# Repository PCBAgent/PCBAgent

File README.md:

# PCBAgent-GX10

PCBAgent takes one circuit request and, with no further input, designs a private board on the ASUS Ascent GX10: simulated, sourced, and routed offline.

A schematic is the product. Part values, pinouts, and the board outline should not have to leave the machine before software can help. PCBAgent runs that work on the GX10, an ultra-small AI computer with the NVIDIA GB10 Grace Blackwell Superchip and 128 GB of unified memory. Nemotron, ngspice, a local JLCPCB catalog, KiCad, and Freerouting all run on the box. Unplugging the network does not stop a design.

## Why local

Cloud schematic tools upload the design before they answer. Here the model and the checkers share the machine where the design is created. There is no cloud round trip, no vendor API for the netlist, and no infrastructure to keep up for a single board. The same flow still runs with the network disconnected.

## What it does

One request becomes a checked board. The model writes the circuit. SPICE, the parts catalog, the placer, and KiCad decide whether that circuit is true. After the first prompt, the run continues on its own until you cancel it, and you can watch placement and routing in KiCad while it does.

1. **Specify and simulate.** `/design` writes a circuit spec and a SKiDL file. SKiDL emits a SPICE netlist, and ngspice runs it. The model does not hand-write a simulator deck.
2. **Verify.** Each acceptance number in the spec, such as output voltage and current, is compared with the ngspice measurement inside the stated tolerance. A value counts only when that simulation produced it. A miss stays inside `/design`: the model changes the circuit and the same checks run again. It does not edit the spec to hide a failure.
3. **Select parts and write the netlist.** Passives and the regulator are matched to a local JLCPCB catalog. Stock, price, and footprint names are copied from that cache and from the installed KiCad libraries. The same connections become a KiCad netlist with those symbols and footprints.
4. **Place and route.** `/layout` asks the model for placement constraints, such as a capacitor next to its IC. It does not emit coordinates or traces. A placer chooses positions, Freerouting draws the copper, and KiCad's design-rule check scores the board. `layout.py --demo` records that sequence and plays it in the PCB editor with no further prompts.

## Demo

Two finished boards are in `designs/`:

- `5v-to-3v3-divider`, a 5 V to 3.3 V divider into a 33 ohm load
- `5v-to-3v3-ldo-10uf-22uf-33ohm-25x20mm-jlcpcb`, the same request on an AMS1117-3.3 with 10 µF in and 22 µF out

Replay the routed board in the KiCad PCB Editor from the GX10 desktop. Enable **Preferences → Plugins → Enable KiCad API** first.

```bash
source .venv/bin/activate
.venv/bin/python skills/layout/demo.py designs/5v-to-3v3-ldo-10uf-22uf-33ohm-25x20mm-jlcpcb --replay
```

Parts move into place, then the copper appears. `layout/board.png` in the same design is the still image of the routed board. To record a new animation while laying out again, run `skills/layout/layout.py designs/<slug> --demo`.

A new design starts in Pi with a single command, for example:

```text
/design 5 V supply to 3.3 V LDO using one linear regulator IC, a 10 µF input capacitor, and a 22 µF output capacitor, output voltage 3.3 V within 0.05 V, output current 0.1 A within 0.01 A into a 33 ohm load, maximum board size 25 mm by 20 mm, JLCPCB
```

## Chat window

The same agent, in its own window instead of the terminal. Skills, commands, and checks are unchanged. On the GX10 desktop:

```bash
python3 chat/window.py
```

`/design` and the rest of the flow work as they do in `pi`. Close the window to stop that session.

## Run it on the GX10

KiCad 9 or newer is installed separately. From this checkout:

```bash
./setup.sh
source .venv/bin/activate
ollama list
```

`setup.sh` installs Pi and `uv` when they are missing, installs SKiDL into `.venv`, and downloads Freerouting 2.5.0. Use an exact model id from `ollama list`. Start the Ollama bridge in one terminal:

```bash
export PCB_OLLAMA_MODEL=<id from ollama list>
.venv/bin/python tools/ollama_bridge.py
```

In another terminal, from this checkout:

```bash
export PCB_OLLAMA_MODEL=<id from ollama list>
pi --provider pcb-ollama --model "$PCB_OLLAMA_MODEL" --thinking off
```

Trust the project when asked. `.pi/settings.json` loads this package. Restart Pi after pulling extension changes, or run `/reload` in a session that is already open. Stop a run yourself with Escape in Pi, or Ctrl+C in a CLI process.

From another machine on the LAN, the GX10 is reached with `ssh <user>@<hostname>.local`, or `ssh <user>@<gx10-ip>` if `.local` does not resolve. At the GX10 keyboard, `whoami`, `hostname`, and `hostname -I` print those values.

## Checks

```bash
.venv/bin/python -m pytest tests -q
node --test tests/test_policy.mjs
```

Stage commands, when you want to run them without the agent:

```bash
.venv/bin/python tools/pcb_stage.py designs/<slug> prepare
.venv/bin/python tools/pcb_stage.py designs/<slug> verify
.venv/bin/python tools/pcb_stage.py designs/<slug> parts
.venv/bin/python tools/pcb_stage.py designs/<slug> netlist
.venv/bin/python skills/layout/layout.py designs/<slug>
```

Each stage prints a short JSON result and writes a full log. Simulation evidence, part ratings, and the netlist report stay next to the design. A passing check covers the measurements and rules the runners implement.

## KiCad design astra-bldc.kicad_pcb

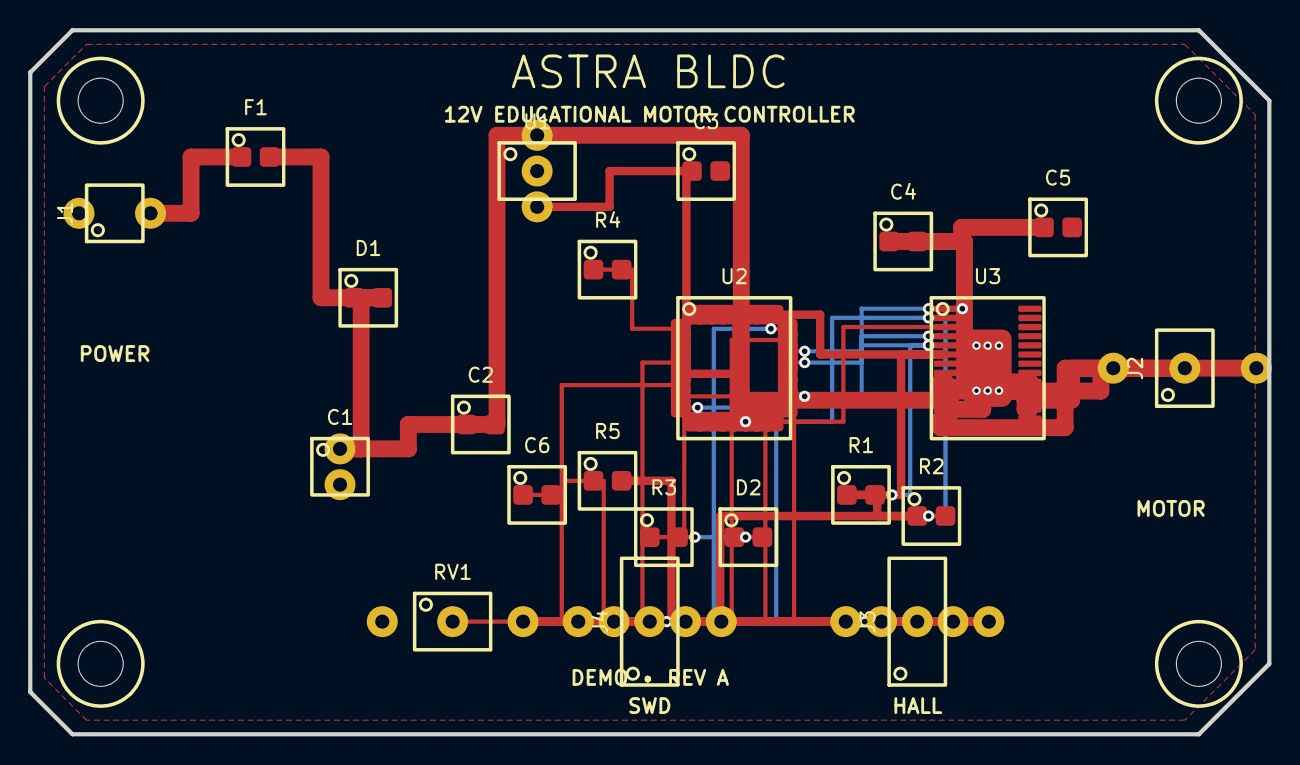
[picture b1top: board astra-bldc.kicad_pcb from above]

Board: 2 copper layers, 88.0 x 50.0 mm, 26 parts (0 on the bottom side), 22 nets.

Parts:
C1: 100uF 25V; CP_Elec_8x10.2
C2, C4, C6: 100nF; C_0603_1608Metric
C3: 10uF; C_0805_2012Metric
C5: 10uF 25V; C_0805_2012Metric
D1: SMBJ18A TVS; D_SMA
D2: GREEN; LED_0603_1608Metric
F1: 2A RESETTABLE; Fuse_1206_3216Metric
H1, H2, H3, H4: M3; MountingHole_3.2mm_M3
J1: POWER IN 12V; TerminalBlock_2_P5.08mm
J2: MOTOR A B C; TerminalBlock_3_P5.08mm
J3: HALL SENSORS; PinHeader_1x05_P2.54mm_Vertical
J4: SWD; PinHeader_1x05_P2.54mm_Vertical
R1, R2, R4, R5: 10k; R_0603_1608Metric
R3: 1k; R_0603_1608Metric
RV1: 10k SPEED; Potentiometer_Alps_RK09K_Single_Horizontal
U1: R-78E3.3-0.5; Converter_DCDC_RECOM_R-78E-0.5_THT
U2: STM32G031K8Tx; LQFP-32_7x7mm_P0.8mm
U3: DRV8313PWP; HTSSOP-28-1EP_4.4x9.7mm_P0.65mm

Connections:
+3V3: C3.1, J3.1, J4.1, R1.1, R2.1, R5.2, RV1.3, U1.3, U2.5, U2.17, U2.32, U3.6
BOOT0: R4.1, U2.1
GND: C1.2, C2.2, C3.2, C4.2, C5.2, C6.2, D1.1, D2.1, J1.2, J3.2, J4.5, R4.2, RV1.1, U1.2, U2.16, U2.31, U3.7, U3.15, U3.21, U3.29
HALL_A: J3.3, U2.7
HALL_B: J3.4, U2.8
HALL_C: J3.5, U2.9
LED_A: D2.2, R3.2
LED_STATUS: R3.1, U2.29
NFAULT: R1.2, U2.22, U3.5
NRST: C6.1, J4.4, R5.1, U2.4
NSLEEP: R2.2, U2.21, U3.1
PHASE_A: J2.1, U3.9, U3.10
PHASE_B: J2.2, U3.13, U3.14
PHASE_C: J2.3, U3.17, U3.18
PWM_A: U2.12, U3.2
PWM_B: U2.14, U3.3
PWM_C: U2.18, U3.4
SPEED: RV1.2, U2.6
SWCLK: J4.3, U2.24
SWDIO: J4.2, U2.23
VBUS: C1.1, C2.1, C4.1, C5.1, D1.2, F1.2, U1.1, U3.11, U3.12, U3.19, U3.20
VIN: F1.1, J1.1

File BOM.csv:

Reference,Value,Footprint,Purpose
J1,POWER IN 12V,TerminalBlock_2_P5.08mm,12 V power input
F1,2A RESETTABLE,Fuse_1206_3216Metric,Input overcurrent protection
D1,SMBJ18A TVS,D_SMA,Input transient clamp
C1,100uF 25V,CP_Elec_8x10.2,Decoupling / bias network
C2,100nF,C_0603_1608Metric,Decoupling / bias network
U1,R-78E3.3-0.5,Converter_DCDC_RECOM_R-78E-0.5_THT,3.3 V logic regulator
C3,10uF,C_0805_2012Metric,Decoupling / bias network
U2,STM32G031K8Tx,LQFP-32_7x7mm_P0.8mm,Motor-control MCU
U3,DRV8313PWP,HTSSOP-28-1EP_4.4x9.7mm_P0.65mm,Three-phase motor driver
C4,100nF,C_0603_1608Metric,Decoupling / bias network
C5,10uF 25V,C_0805_2012Metric,Decoupling / bias network
R1,10k,R_0603_1608Metric,Decoupling / bias network
R2,10k,R_0603_1608Metric,Decoupling / bias network
R3,1k,R_0603_1608Metric,Decoupling / bias network
D2,GREEN,LED_0603_1608Metric,Status indicator
RV1,10k SPEED,Potentiometer_Alps_RK09K_Single_Horizontal,Speed command
J2,MOTOR A B C,TerminalBlock_3_P5.08mm,BLDC phase output
J3,HALL SENSORS,PinHeader_1x05_P2.54mm_Vertical,Hall sensor interface
J4,SWD,PinHeader_1x05_P2.54mm_Vertical,SWD programming/debug
R4,10k,R_0603_1608Metric,Decoupling / bias network
R5,10k,R_0603_1608Metric,Decoupling / bias network
C6,100nF,C_0603_1608Metric,Decoupling / bias network

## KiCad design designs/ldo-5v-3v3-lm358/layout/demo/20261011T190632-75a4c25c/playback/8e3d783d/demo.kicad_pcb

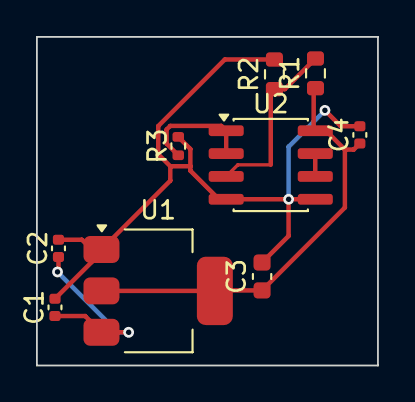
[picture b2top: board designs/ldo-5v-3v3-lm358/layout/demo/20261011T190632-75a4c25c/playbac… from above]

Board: 2 copper layers, 18.9 x 18.3 mm, 9 parts (0 on the bottom side), 6 nets.

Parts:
C1: 10uF; C_0402_1005Metric
C2, C4: 100nF; C_0402_1005Metric
C3: 22uF; C_0603_1608Metric
R1, R2: 10k; R_0603_1608Metric
R3: 33; R_0402_1005Metric
U1: AMS1117-3.3; SOT-223-3_TabPin2
U2: LM358; SOIC-8_3.9x4.9mm_P1.27mm

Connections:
DIV_MID: R1.2, R2.1, U2.3
GND: C1.2, C2.2, C3.2, C4.2, R2.2, R3.2, U1.1, U2.4, U2.5
LDO_OUT: C3.1, C4.1, R1.1, U1.2, U2.8
UNUSED: U2.6, U2.7
VIN: C1.1, C2.1, U1.3
VOUT: R3.1, U2.1, U2.2

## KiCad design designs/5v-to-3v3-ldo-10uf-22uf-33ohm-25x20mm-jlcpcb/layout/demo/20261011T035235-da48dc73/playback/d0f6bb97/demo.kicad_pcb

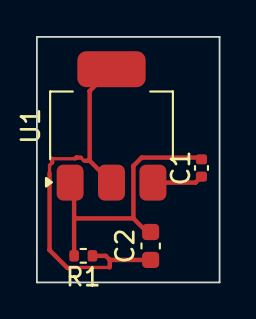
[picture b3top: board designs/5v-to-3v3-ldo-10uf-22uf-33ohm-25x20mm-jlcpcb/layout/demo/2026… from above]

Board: 2 copper layers, 10.1 x 13.6 mm, 4 parts (0 on the bottom side), 3 nets.

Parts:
C1: 10uF 6.3V X5R ±20% 0402 Multilayer Ceramic Capaci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; C_0402_1005Metric
C2: 22uF 6.3V X5R ±20% 0603 Multilayer Ceramic Capaci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; C_0603_1608Metric
R1: -55℃~+155℃ 33Ω 50V 62.5mW Thick Film Resistor ±1%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; R_0402_1005Metric
U1: -40℃~+125℃ 0.003%Vout 1 1.1V@(800mA) 15V 1A 3.3V 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; SOT-223-3_TabPin2

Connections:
GND: C1.2, C2.2, R1.2, U1.1
VIN: C1.1, U1.3
VOUT: C2.1, R1.1, U1.2

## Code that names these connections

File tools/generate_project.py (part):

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    ("D2", "GREEN", "LED_0603_1608Metric", [("1", "GND"), ("2", "LED_A")]),
    ("RV1", "10k SPEED", "Potentiometer_Alps_RK09K_Single_Horizontal", [("1", "GND"), ("2", "SPEED"), ("3", "+3V3")]),
    ("J2", "MOTOR A B C", "TerminalBlock_3_P5.08mm", [("1", "PHASE_A"), ("2", "PHASE_B"), ("3", "PHASE_C")]),
    ("J3", "HALL SENSORS", "PinHeader_1x05_P2.54mm_Vertical", [("1", "+3V3"), ("2", "GND"), ("3", "HALL_A"), ("4", "HALL_B"), ("5", "HALL_C")]),
    ("J4", "SWD", "PinHeader_1x05_P2.54mm_Vertical", [("1", "+3V3"), ("2", "SWDIO"), ("3", "SWCLK"), ("4", "NRST"), ("5", "GND")]),
    ("R4", "10k", "R_0603_1608Metric", [("1", "BOOT0"), ("2", "GND")]),
    ("R5", "10k", "R_0603_1608Metric", [("1", "NRST"), ("2", "+3V3")]),
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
